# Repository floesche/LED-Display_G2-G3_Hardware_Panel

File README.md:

---
title: Hardware
parent: Generation 2
---

This repository is related to the Panels project.  It includes the PCB design files, BOM, and datasheets for the (Gen-2) 8x8 LED Panels.

## Project content

```
├── fab_v1p3
└── pcb
    ├── datasheets
    ├── gerber_v1p0
    ├── gerber_v1p1
    ├── gerber_v1p2
    ├── gerber_v1p3
    ├── libs
    ├── mods
    └── old_bom
```

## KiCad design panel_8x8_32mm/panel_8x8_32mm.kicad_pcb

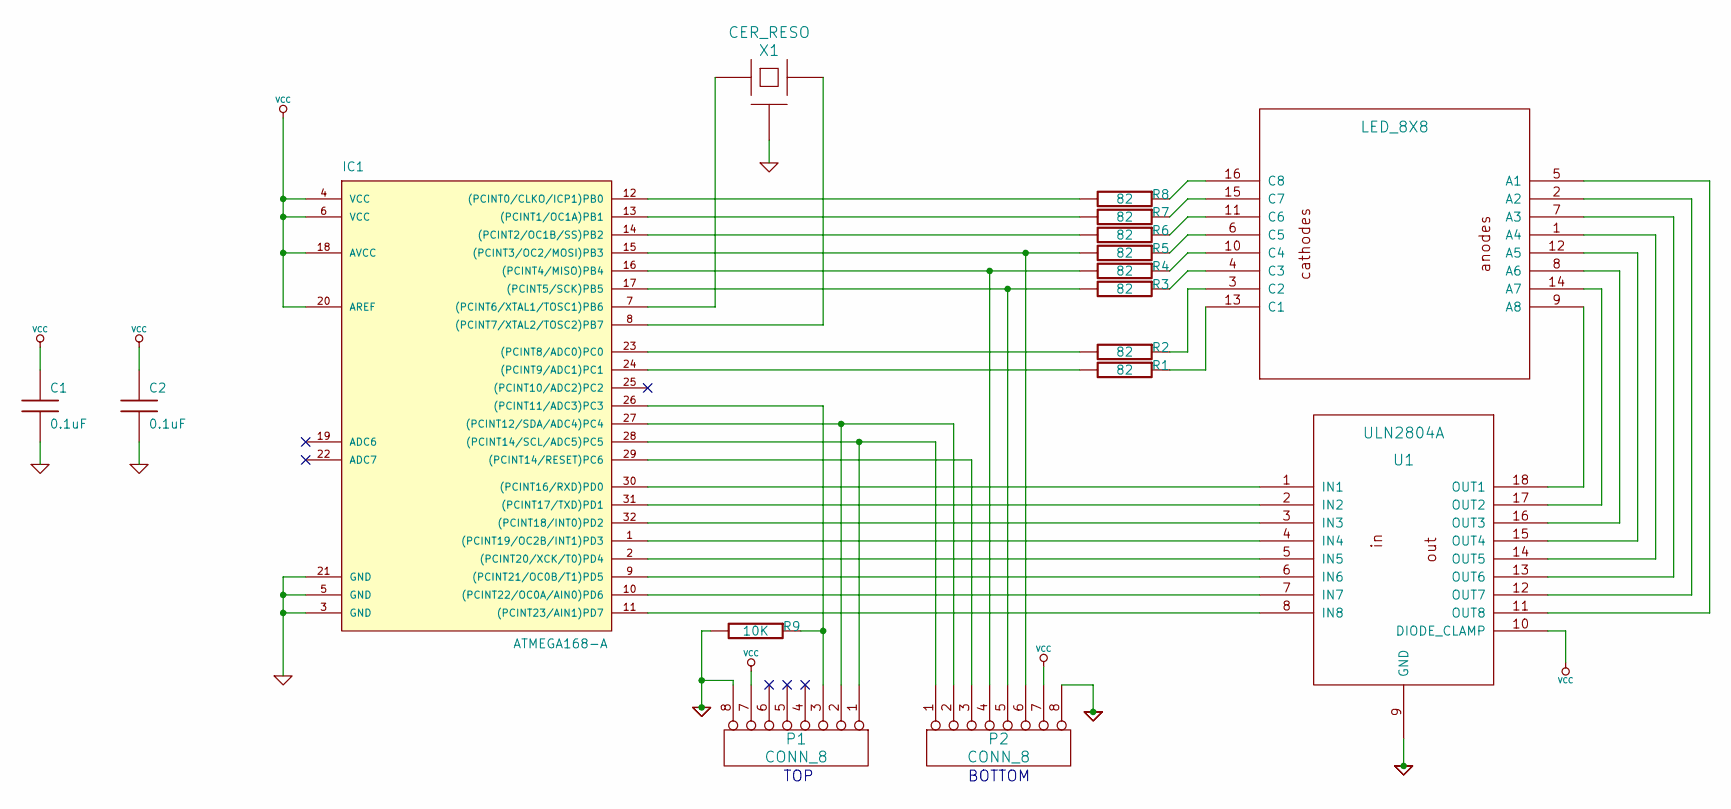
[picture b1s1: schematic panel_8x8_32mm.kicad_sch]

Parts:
C1, C2: 0.1uF
IC1: ATMEGA168-A; TQFP32
P1, P2: CONN_8
R1, R2, R3, R4, R5, R6, R7, R8: 82
R9: 10K
U1: ULN2804A
X1: CER_RESO

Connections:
GND: C1.2, C2.2, IC1.3 (GND), IC1.5 (GND), IC1.21 (GND), P1.8, P2.8, R9.2, U1.9 (GND), X1.2 (GND)
unnamed 1: R2.1; also elsewhere on the board
unnamed: IC1.28 ((PCINT14/SCL/ADC5)PC5), P1.1, P2.1
unnamed 3: U1.14 (OUT5); also elsewhere on the board
unnamed 4: U1.16 (OUT3); also elsewhere on the board
unnamed: IC1.27 ((PCINT12/SDA/ADC4)PC4), P1.2, P2.2
unnamed: IC1.16 ((PCINT4/MISO)PB4), P2.4, R4.2
unnamed: IC1.15 ((PCINT3/OC2/MOSI)PB3), P2.6, R5.2
unnamed: IC1.2 ((PCINT20/XCK/T0)PD4), U1.5 (IN5)
unnamed: IC1.8 ((PCINT7/XTAL2/TOSC2)PB7), X1.3
unnamed: IC1.9 ((PCINT21/OC0B/T1)PD5), U1.6 (IN6)
unnamed: IC1.10 ((PCINT22/OC0A/AIN0)PD6), U1.7 (IN7)
unnamed: IC1.30 ((PCINT16/RXD)PD0), U1.1 (IN1)
unnamed: IC1.11 ((PCINT23/AIN1)PD7), U1.8 (IN8)
unnamed: IC1.31 ((PCINT17/TXD)PD1), U1.2 (IN2)
unnamed: IC1.12 ((PCINT0/CLKO/ICP1)PB0), R8.2
unnamed: IC1.1 ((PCINT19/OC2B/INT1)PD3), U1.4 (IN4)
unnamed: IC1.32 ((PCINT18/INT0)PD2), U1.3 (IN3)
unnamed: IC1.23 ((PCINT8/ADC0)PC0), R2.2
unnamed: IC1.24 ((PCINT9/ADC1)PC1), R1.2
unnamed: IC1.26 ((PCINT11/ADC3)PC3), P1.3, R9.1
unnamed: IC1.29 ((PCINT14/RESET)PC6), P2.3
unnamed 22: U1.11 (OUT8); also elsewhere on the board
unnamed 23: U1.18 (OUT1); also elsewhere on the board
unnamed: IC1.14 ((PCINT2/OC1B/SS)PB2), R6.2
unnamed 25: R5.1; also elsewhere on the board
unnamed: IC1.13 ((PCINT1/OC1A)PB1), R7.2
unnamed 27: R3.1; also elsewhere on the board
unnamed 28: U1.13 (OUT6); also elsewhere on the board
unnamed 29: R4.1; also elsewhere on the board
unnamed 30: R6.1; also elsewhere on the board
unnamed 31: U1.15 (OUT4); also elsewhere on the board
unnamed 32: R1.1; also elsewhere on the board
unnamed 33: U1.17 (OUT2); also elsewhere on the board
unnamed 34: R7.1; also elsewhere on the board
unnamed 35: R8.1; also elsewhere on the board
unnamed 36: U1.12 (OUT7); also elsewhere on the board
unnamed: IC1.7 ((PCINT6/XTAL1/TOSC1)PB6), X1.1
unnamed: IC1.17 ((PCINT5/SCK)PB5), P2.5, R3.2
VCC: C1.1, C2.1, IC1.4 (VCC), IC1.6 (VCC), IC1.18 (AVCC), IC1.20 (AREF), P1.7, P2.7, U1.10 (DIODE_CLAMP)

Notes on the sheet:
TOP
BOTTOM

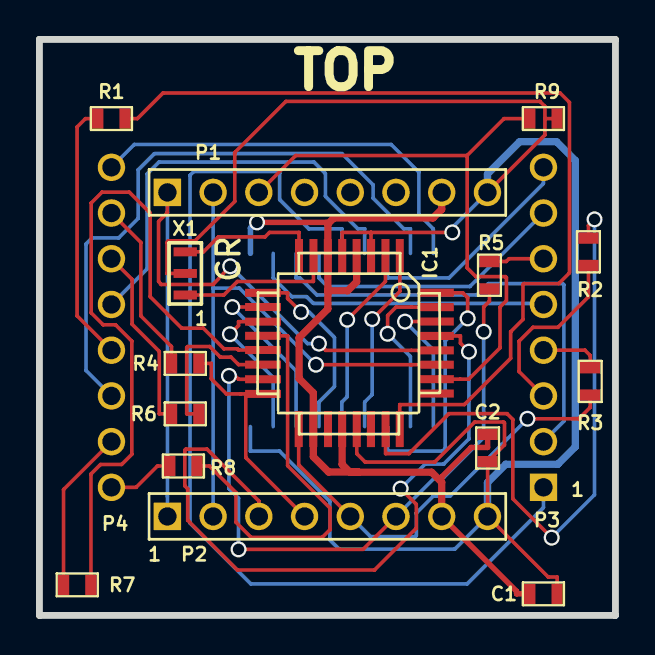
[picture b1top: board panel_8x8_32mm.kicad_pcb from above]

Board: 2 copper layers, 32.0 x 32.0 mm, 17 parts (1 on the bottom side), 40 nets.

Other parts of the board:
MATRIX1: LED_8X8; LED_8x8

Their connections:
unnamed 1: MATRIX1.3; also elsewhere on the board
unnamed 3: MATRIX1.1; also elsewhere on the board
unnamed 4: MATRIX1.8; also elsewhere on the board
unnamed 22: MATRIX1.5; also elsewhere on the board
unnamed 23: MATRIX1.9; also elsewhere on the board
unnamed 25: MATRIX1.6; also elsewhere on the board
unnamed 27: MATRIX1.4; also elsewhere on the board
unnamed 28: MATRIX1.7; also elsewhere on the board
unnamed 29: MATRIX1.10; also elsewhere on the board
unnamed 30: MATRIX1.11; also elsewhere on the board
unnamed 31: MATRIX1.12; also elsewhere on the board
unnamed 32: MATRIX1.13; also elsewhere on the board
unnamed 33: MATRIX1.14; also elsewhere on the board
unnamed 34: MATRIX1.15; also elsewhere on the board
unnamed 35: MATRIX1.16; also elsewhere on the board
unnamed 36: MATRIX1.2; also elsewhere on the board

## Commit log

2020-08-06 getting ready for panel page
2020-11-16 restructure repository
2020-11-18 file cleanup
2020-11-19 improve documentation for g2 panels
2020-11-20 small additoin
2021-11-10 add assets
2021-11-11 consistent file naming
2021-11-11 improve documentation
2021-11-11 integrate datasheets better
2021-11-12 add older panel schematics
2021-11-19 fix links
2021-11-29 correct header
2021-11-30 consistent documentation
2022-05-23 fix link
2022-05-27 fix text
2022-11-08 migrate to KiCad 6
